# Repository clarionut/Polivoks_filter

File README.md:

# Polivoks_filter
A Eurorack version of the famous Polivoks filter

Here is the original schematic of the filter portion of the Polivoks filter board (the remainder of the board is an envelope generator for modulation of the filter cutoff) -

(1: CV input, 2: Audio input, 3: BP out / resonance, 4: LP out)

It's a deceptively simple circuit based on two К140УД12 programmable op-amps as the non-linear elements, using their variable slew rate as the basis of the filter. The КР140УД8Б is a simple general-purpose op-amp to mix the control voltages, and the КТ315Г is a general purpose NPN transistor which controls the programming current to the К140УД12 chips. The К140УД12 was a soviet-era copy of the uA776 so I hoped that using an MC1776 (a more modern equivalent) would work OK. Other copies of the filter (e.g. by [Marc Bareille](http://m.bareille.free.fr/modular1/vcf_polivoks/vcf_polivoks.htm)) have used a TL072 in place of the КР140УД8Б and a 2N3904 in place of the КТ315Г. I made these substitutions and found that the circuit worked well on a breadboard.

For use in a modular synth the circuit also needs inputs and outputs (unlike the hard-wired signal paths in the Polivoks). I decided to have two CV inputs, one with an attenuverter (the idea came from Marc Bareille's circuit but the implementation is completely different). The behaviour of the filter is rather dependent on the input signal amplitude so I added a passive attenuator on the audio input. There are separate buffers for the lowpass and bandpass outputs plus an (approximately) equal-power mixer giving a third output continuously variable between LP and BP.

I particularly wanted to give this module a convincing Polivoks style so I decided to label it in white on a black background with Russian legends and graphic elements based on the real Polivoks. The graphics I used are in the Panel folder (Polivoks.svg) but I've also included a version with legends in English (Polivoks_EN.svg).

I also 3D printed some Polivoks-inspired (but Eurorack sized) [knobs for the potentiometers](https://www.thingiverse.com/thing:7183551) and am very pleased with the final result.

The sound is very similar to my original Polivoks over most of its range, though the self-oscillation behaviour at extreme resonance settings is slightly wilder than the original.

There are PDFs of the schematic and PCB layout in the Schematics folder along with a copy of the KiCad project. The KiCad project uses some custom symbols, so you may need to download my [custom KiCad libraries](https://github.com/clarionut/kiCad_libraries) and tell KiCad where to find them.

I've also included the Gerbers in case anyone wants to use my PCB layout without any changes.

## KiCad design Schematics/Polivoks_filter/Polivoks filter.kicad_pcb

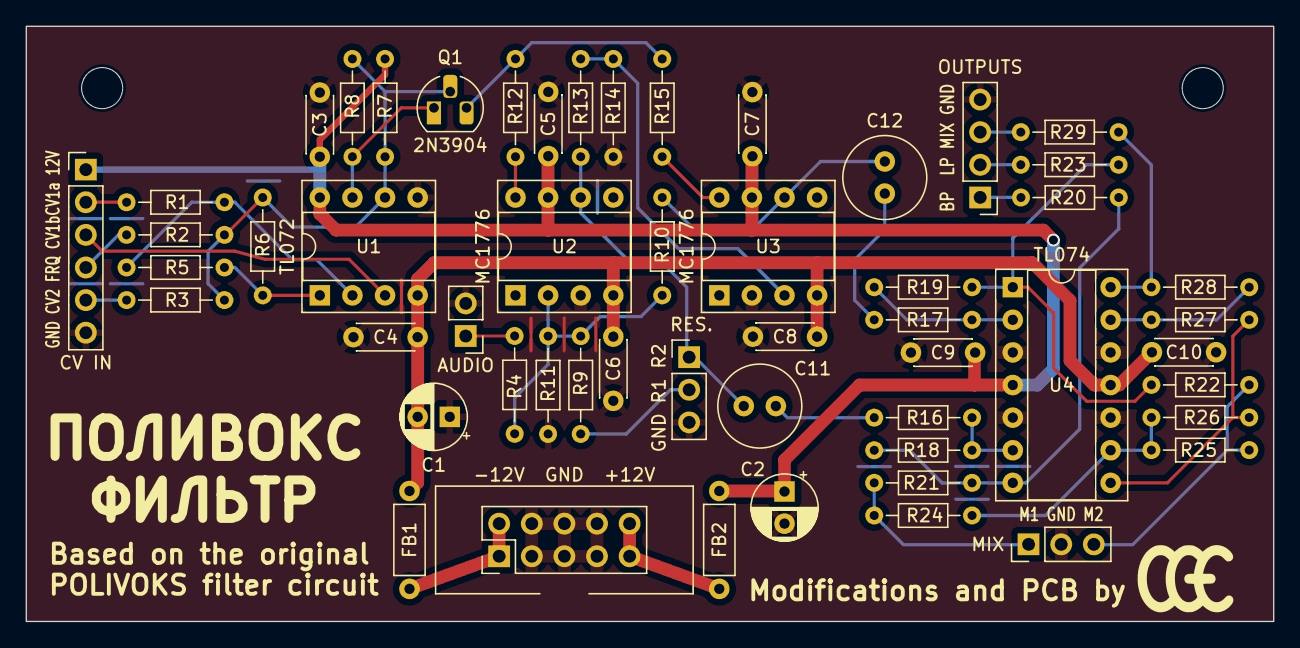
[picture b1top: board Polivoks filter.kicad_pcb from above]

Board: 2 copper layers, 97.2 x 46.4 mm, 55 parts (0 on the bottom side), 37 nets.

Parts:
C1, C2: 10u; CP_Radial_D5.0mm_P2.50mm
C3, C4, C5, C6, C7, C8, C9, C10: 100n; C_Disc_D4.3mm_W1.9mm_P5.00mm
C11, C12: 10u; C_Radial_D6.3mm_H7.0mm_P2.50mm
FB1, FB2: FB; L_Axial_L5.3mm_D2.2mm_P7.62mm_Horizontal_Vishay_IM-1
J1: CV IN; PinHeader_1x06_P2.54mm_Vertical
J2: RESONANCE; PinHeader_1x03_P2.54mm_Vertical
J3: POWER; Power_2x05
J4: OUTPUTS; PinHeader_1x04_P2.54mm_Vertical
J12: AUDIO; PinHeader_1x02_P2.54mm_Vertical
J13: MIX; PinHeader_1x03_P2.54mm_Vertical
Q1: 2N3904; TO-92_HandSolder
R1, R3, R5, R7, R18, R19, R27, R28: 100k; R_Axial_DIN0204_L3.6mm_D1.6mm_P7.62mm_Horizontal
R2: 180k; R_Axial_DIN0204_L3.6mm_D1.6mm_P7.62mm_Horizontal
R4, R6, R9, R10, R13: 47k; R_Axial_DIN0204_L3.6mm_D1.6mm_P7.62mm_Horizontal
R8: 3k; R_Axial_DIN0204_L3.6mm_D1.6mm_P7.62mm_Horizontal
R11, R14, R20, R23, R29: 1k; R_Axial_DIN0204_L3.6mm_D1.6mm_P7.62mm_Horizontal
R12, R15: 110k; R_Axial_DIN0204_L3.6mm_D1.6mm_P7.62mm_Horizontal
R16: 62k; R_Axial_DIN0204_L3.6mm_D1.6mm_P7.62mm_Horizontal
R17: 75k; R_Axial_DIN0204_L3.6mm_D1.6mm_P7.62mm_Horizontal
R21, R22, R24, R25: 68k; R_Axial_DIN0204_L3.6mm_D1.6mm_P7.62mm_Horizontal
R26: 240k; R_Axial_DIN0204_L3.6mm_D1.6mm_P7.62mm_Horizontal
REFe: CGE_logo; CGE_logo_med
U1: TL072; DIP-8_W7.62mm_Socket
U2, U3: MC1776; DIP-8_W7.62mm_Socket
U4: TL074; DIP-14_W7.62mm_Socket

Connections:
+12V: C2.1, C3.1, C5.1, C7.1, C9.1, FB2.1, J1.1, R7.1, U1.8 (V+), U2.7 (V+), U3.7 (V+), U4.4 (V+)
-12V: C1.2, C4.1, C6.1, C8.1, C10.1, FB1.1, U1.4 (V-), U2.4 (V-), U3.4 (V-), U4.11 (V-)
/AUDIO_IN: J12.1, R4.2
/BPO: J4.1, R20.1
/CV1_A: J1.2, R1.2
/CV1_B: J1.3, U1.3 (+)
/CV2: J1.5, R3.2
/FRQ: J1.4, R2.2
/LPO: J4.2, R23.1
/MIX: J4.3, R29.1
/MIX1: J13.1, R21.1, R24.2
/MIX2: J13.3, R22.1, R25.2
/RES1: C11.1, J2.1, R13.2, U2.6
/RES2: J2.2, R9.2
GND: C1.1, C2.2, C3.2, C4.2, C5.2, C6.2, C7.2, C8.2, C9.2, C10.2, J1.6, J2.3, J3.3, J3.4, J3.5, J3.6, J3.7, J3.8, J4.4, J12.2, J13.2, R11.2, R14.2, U1.5 (+), U2.3 (+), U3.2 (-), U4.3 (+), U4.5 (+), U4.10 (+), U4.12 (+)
unnamed: C11.2, R16.2
unnamed: C12.1, R10.1, U3.6
unnamed: C12.2, R17.2
unnamed: FB1.2, J3.1, J3.2
unnamed: FB2.2, J3.9, J3.10
unnamed: Q1.2 (B), R2.1, R3.1, R6.1, R7.2, R8.1, U1.6 (-)
unnamed: Q1.3 (C), R12.1, R15.1
unnamed: Q1.1 (E), R8.2, U1.7
unnamed: R5.1, R6.2, U1.1
unnamed: R18.1, R20.2, R21.2, U4.7
unnamed: R19.1, R22.2, R23.2, U4.1
unnamed: R26.1, R27.2, U4.8
unnamed: R28.1, R29.2, U4.14
unnamed: R1.1, R5.2, U1.2 (-)
unnamed: R4.1, R9.1, R10.2, R11.1, U2.2 (-)
unnamed: R12.2, U2.8 (Iset)
unnamed: R13.1, R14.1, U3.3 (+)
unnamed: R15.2, U3.8 (Iset)
unnamed: R17.1, R19.2, U4.2 (-)
unnamed: R16.1, R18.2, U4.6 (-)
unnamed: R24.1, R25.1, R26.2, U4.9 (-)
unnamed: R27.1, R28.2, U4.13 (-)

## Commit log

2025-10-26 Create tmp
2025-10-27 Rename README to README.md
